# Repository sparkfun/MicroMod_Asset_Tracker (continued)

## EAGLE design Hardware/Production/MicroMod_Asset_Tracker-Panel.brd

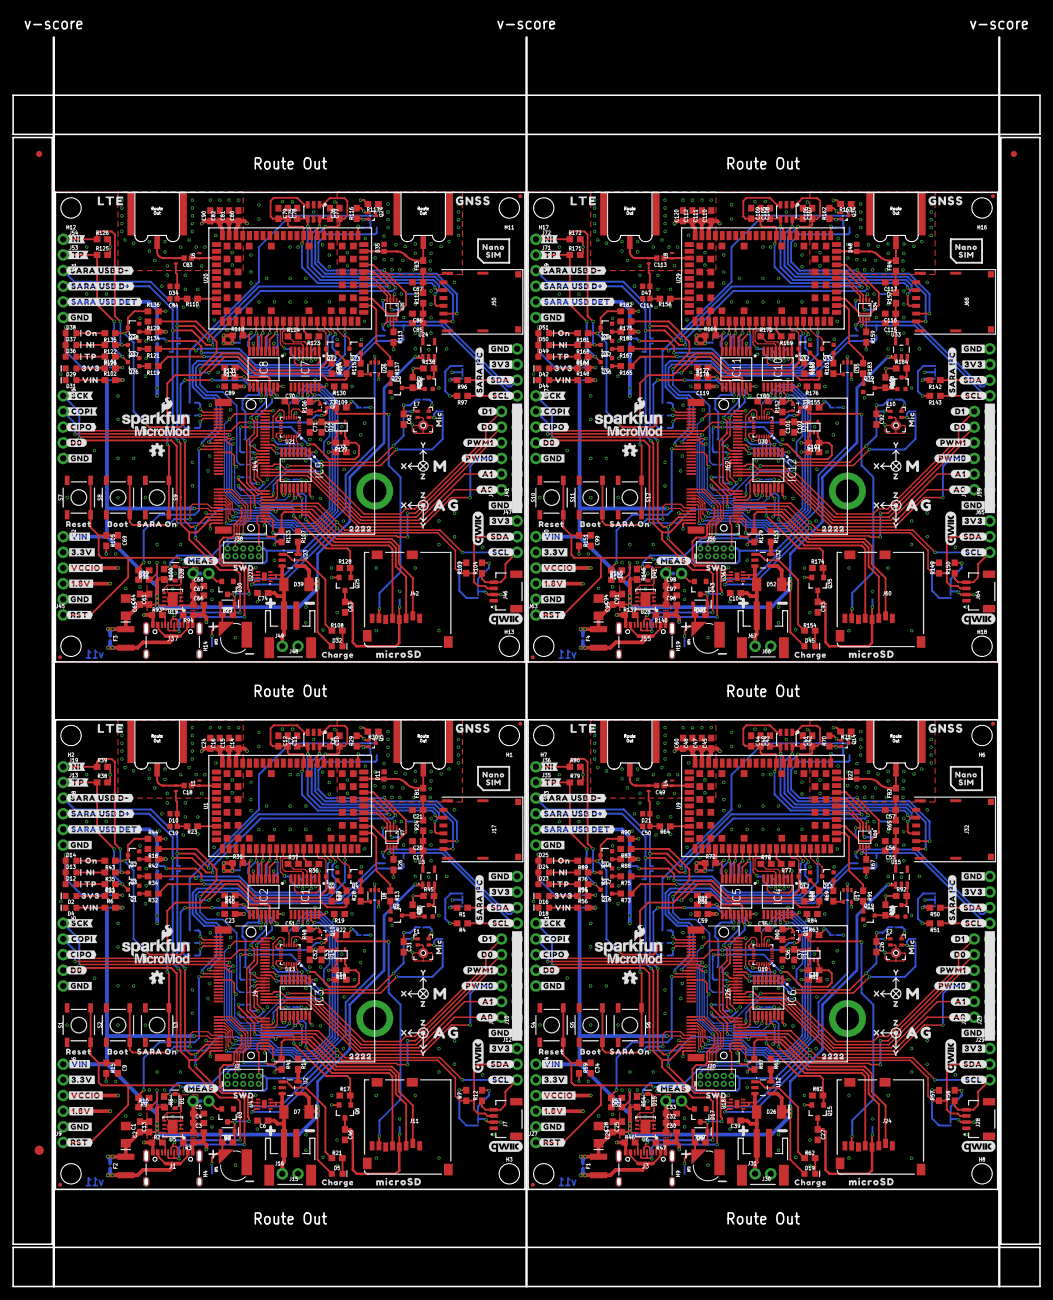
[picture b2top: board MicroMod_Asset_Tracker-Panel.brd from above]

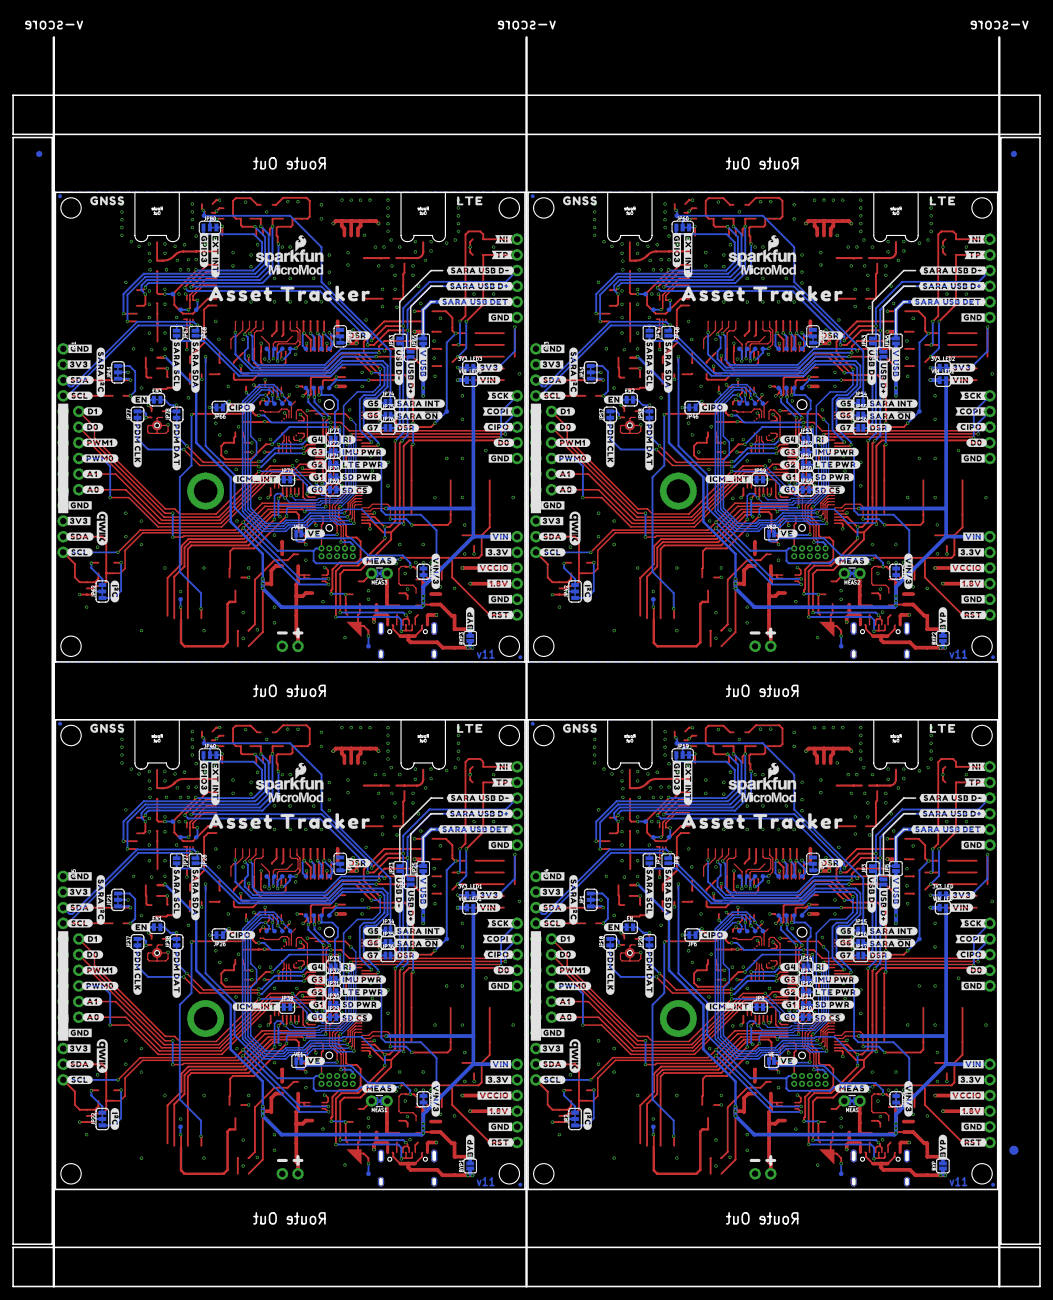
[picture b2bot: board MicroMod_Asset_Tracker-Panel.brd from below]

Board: 4 copper layers, 166.6 x 202.7 mm, 1354 parts (515 on the bottom side), 548 nets.

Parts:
3V3_LED, 3V3_LED1, 3V3_LED2, 3V3_LED3: SMT-JUMPER_2_NC_TRACE_SILK
BT1, BT2, BT3, BT4: ML414H; ML414H_IV01E
BYP, BYP1, BYP2, BYP3: JUMPER-SMT_2_NO_SILK; SMT-JUMPER_2_NO_SILK
C1, C4, C12, C14, C20, C22, C23, C26, C27, C28, C31, C32, C35, C36, C44, C45, C46, C51, C52, C56, C58, C59, C62, C63, C64, C67, C70, C71, C79, C80, C86, C88, C89, C92, C93, C94, C97, C100, C101, C109, C110, C116, C118, C119: 0.1uF; 0603
C2, C29, C65, C95: 10uF; EIA3216
C3, C6, C30, C39, C66, C74, C96, C104: 4.7uF; 0603
C5, C13, C25, C33, C61, C68, C91, C98: 0.22uF; 0603
C7, C8, C10, C11, C21, C40, C41, C42, C43, C57, C75, C76, C77, C78, C87, C105, C106, C107, C108, C117: 47pF; 0603
C9, C34, C69, C99: 1nF; 0603
C15, C47, C81, C111: 68pF; 0603
C16, C48, C82, C112: 10uF; 0603
C17, C37, C38, C53, C54, C55, C72, C73, C85, C102, C103, C115: 1.0uF; 0603
C18, C49, C83, C113: 33pF; 0402
C19, C50, C84, C114: 27pF; 0402
C24, C60, C90, C120: 15pF; 0603
D1, D15, D28, D41: 3.3V; SOD-323
D2, D16, D29, D42: RED; LED-0603
D3, D17, D30, D43: BAS70-05; SOT23-3
D4, D5, D18, D19, D31, D32, D44, D45: Yellow; LED-0603
D6, D9, D27, D40: 3A/10V/280mV; SOD-323
D7, D26, D39, D52: 1A/15V/220mV; DO-214BA
D8, D20, D33, D46: DT1042-04SO-7; SOT23-6L
D10, D11, D21, D22, D34, D35, D47, D48: PESD0402; 0402
D12, D23, D36, D49: GREEN; LED-0603
D13, D24, D37, D50: BLUE; LED-0603
D14, D25, D38, D51: WHITE; LED-0603
DSR, DSR1, DSR2, DSR3: JUMPER-SMT_3_1-NC_TRACE_SILK; SMT-JUMPER_3_1-NC_TRACE_SILK
E1, E2, E7, E10: SPH0641LM4H-1; SPH0641LM4H-1_MICROPHONE
E3, E5, E8, E11: LTE; SMA-EDGE-SMD
E4, E6, E9, E12: GNSS; SMA-EDGE-SMD
E$1, E$2, E$3, E$4: FIDUCIAL-1X2
E$5, E$6: FIDUCIAL-1.5X3
EN, EN1, EN2, EN3: SMT-JUMPER_2_NC_TRACE_SILK
F1, F2, F3, F4: 6V/2A; 1210
FB1, FB2, FB3, FB4: 30Ω/1.8A; 0603
FD1, FD2, FD3, FD4, FD5, FD6, FD7, FD8, FD9, FD10, FD11, FD12, FD13, FD14, FD15, FD16: FIDUCIALUFIDUCIAL; FIDUCIAL-MICRO
H1, H2, H3, H4, H6, H7, H8, H9, H11, H12, H13, H14, H16, H17, H18, H19: STAND-OFF
H5, H10, H15, H20: STAND-OFF-REFLOW2.5MM_TALL; STAND-OFF-REFLOW-M2.5
IC1, IC2, IC3, IC4, IC5, IC6, IC7, IC8, IC9, IC10, IC11, IC12: SN74AVC4T774PW; SOP65P640X120-16N
J1, J3, J37, J55: USB-C-16P_4LAYER-PADS
J2, J20, J38, J56: JTAG; 2X5-PTH-1.27MM
J4, J26, J44, J62: MICROMOD-2222-C; M.2-CONNECTOR-E
J5, J21, J39, J57: SPI; 1X05_NO_SILK
J6, J34, J52, J70: DIAG; 1X05_NO_SILK
J7, J28, J46, J64: QWIIC_RIGHT_ANGLE; JST04_1MM_RA
J8, J10, J22, J23, J40, J41, J58, J59: 1X06_NO_SILK
J9, J27, J45, J63: !RST!; 1X01_NO_SILK
J11, J24, J42, J60: microSD; MICRO-SD-SOCKET
J12, J14, J25, J29, J43, J47, J61, J65: 1X04_NO_SILK
J13, J35, J53, J71: TP; 1X01_NO_SILK
J15, J30, J48, J66: JST-2-SMD
J16, J31, J49, J67: 1X02_NO_SILK
J17, J32, J50, J68: NANO_SIM; NANO_SIM_WURTH_693043020611
J18, J33, J51, J69: SARA_USB; 1X04_NO_SILK
J19, J36, J54, J72: NI; 1X01_NO_SILK
JP1, JP2, JP21, JP22, JP41, JP42, JP61, JP62: SMT-JUMPER_3_2-NC_TRACE_SILK
JP3, JP4, JP5, JP7, JP8, JP13, JP14, JP15, JP16, JP17, JP23, JP24, JP25, JP27, JP28, JP32, JP33, JP34, JP35, JP36, JP43, JP44, JP45, JP47, JP48, JP52, JP53, JP54, JP55, JP56, JP63, JP64, JP65, JP67, JP68, JP72, JP73, JP74, JP75, JP76: JUMPER-SMT_2_NO_SILK; SMT-JUMPER_2_NO_SILK
JP6, JP9, JP10, JP11, JP12, JP18, JP20, JP26, JP29, JP30, JP31, JP37, JP38, JP39, JP46, JP49, JP50, JP51, JP57, JP58, JP59, JP66, JP69, JP70, JP71, JP77, JP78, JP79: JUMPER-SMT_2_NC_TRACE_SILK; SMT-JUMPER_2_NC_TRACE_SILK
JP19, JP40, JP60, JP80: JUMPER-SMT_3_1-NC_TRACE_SILK; SMT-JUMPER_3_1-NC_TRACE_SILK
L1, L4, L6, L8: DNP; 0402_COILCRAFT
L2, L3, L5, L7: 68nH; 0402_COILCRAFT
LOGO1, LOGO4, LOGO5, LOGO10, LOGO13, LOGO16, LOGO19, LOGO22: SFE_LOGO_NAME_FLAME.1_INCH; SFE_LOGO_NAME_FLAME_.1
LOGO2, LOGO6, LOGO7, LOGO8, LOGO11, LOGO12, LOGO14, LOGO17, LOGO18, LOGO20, LOGO23, LOGO24: QWIIC_LOGO_CONNECTOR; QWIIC_5.5MM
LOGO3, LOGO9, LOGO15, LOGO21: OSHW-LOGOMINI; OSHW-LOGO-MINI
MEAS, MEAS1, MEAS2, MEAS3: COMBO-JUMPER_2_NC_TRACE
Q1, Q2, Q3, Q4, Q7, Q8, Q9, Q12, Q13, Q16, Q17, Q18, Q19, Q20, Q22, Q23, Q26, Q27, Q28, Q29, Q30, Q32, Q33, Q36, Q37, Q38, Q39, Q40: 310mA/60V/1.6Ω; SOT323
Q5, Q10, Q11, Q14, Q21, Q24, Q31, Q34: 20V/0.2A/8MHz/1.2Ω/1Vth; SOT-416FL
Q6, Q15, Q25, Q35: 20V/4.2A/52mΩ/1.4W; SOT23-3
R1, R4, R7, R12, R14, R22, R29, R30, R48, R50, R51, R57, R58, R60, R61, R63, R70, R71, R96, R97, R103, R104, R106, R107, R109, R116, R117, R142, R143, R149, R150, R152, R153, R155, R162, R163: 2.2k; 0603
R2, R3, R46, R47, R93, R94, R139, R140: 5.1k; 0603
R5, R15, R16, R17, R18, R19, R20, R25, R38, R39, R40, R41, R44, R45, R54, R59, R66, R79, R80, R81, R82, R83, R84, R85, R86, R87, R90, R92, R100, R105, R112, R125, R126, R127, R128, R129, R130, R131, R132, R133, R136, R138, R146, R151, R158, R171, R172, R173, R174, R175, R176, R177, R178, R179, R182, R184: 100k; 0603
R6, R56, R102, R148: 4.7k; 0603
R8, R49, R95, R141: 3.3k; 0603
R9, R23, R52, R64, R98, R110, R144, R156: 10k; 0603
R10, R53, R99, R145: 20k; 0603
R11, R13, R21, R27, R28, R32, R34, R42, R43, R55, R62, R68, R69, R73, R75, R88, R89, R91, R101, R108, R114, R115, R119, R121, R134, R135, R137, R147, R154, R160, R161, R165, R167, R180, R181, R183: 1k; 0603
R24, R65, R111, R157: 10; 0603
R26, R67, R113, R159: 200k; 0603
R31, R36, R37, R72, R77, R78, R118, R123, R124, R164, R169, R170: 0; 0603
R33, R74, R120, R166: 100; 0603
R35, R76, R122, R168: 470; 0603
S1, S4, S7, S10: RESET; TACTILE_SWITCH_SMD_5.2MM
S2, S5, S8, S11: BOOT; TACTILE_SWITCH_SMD_5.2MM
S3, S6, S9, S12: SARA_PWR; TACTILE_SWITCH_SMD_5.2MM
TP1, TP2, TP3, TP4, TP5, TP6, TP7, TP8, TP9, TP10, TP11, TP12, TP13, TP14, TP15, TP16, TP17, TP18, TP19, TP20, TP21, TP22, TP23, TP24, TP25, TP26, TP27, TP28, TP29, TP30, TP31, TP32, TP33, TP34, TP35, TP36, TP37, TP38, TP39, TP40, TP41, TP42, TP43, TP44, TP45, TP46, TP47, TP48, TP49, TP50, TP51, TP52, TP53, TP54, TP55, TP56, TP57, TP58, TP59, TP60, TP61, TP62, TP63, TP64, TP65, TP66, TP67, TP68, TP69, TP70, TP71, TP72, TP73, TP74, TP75, TP76, TP77, TP78, TP79, TP80, TP81, TP82, TP83, TP84, TP85, TP86, TP87, TP88, TP89, TP90, TP91, TP92: TEST-POINT3; PAD.03X.03
U1, U9, U20, U29: SARA-R5; SARA-LGA
U2, U12, U23, U32: MCP73831; SOT23-5
U3, U15, U24, U33: 3.3V; SOT23-5
U4, U18, U27, U36: MAX17048; DFN-8
U5, U6, U19, U28: AP7361C-33FGE; UDFN-8
U7, U16, U25, U34: PCA9306; VSSOP_8PIN
U8, U17, U26, U35: 74HC1G04; SOT353
U10, U13, U21, U30: 9DoF IMU; QFN24-3X3-ICM-20948
U11, U14, U22, U31: 1.8V/100mA; SC70
U$1, U$223, U$354, U$485: #EN#0
U$2, U$222, U$353, U$484: MIC0
U$3, U$11, U$13, U$14, U$156, U$157, U$179, U$180, U$287, U$288, U$310, U$311, U$418, U$419, U$441, U$442: #3V3#1
U$4, U$176, U$307, U$438: #3V3#0
U$5, U$23, U$224, U$225, U$355, U$356, U$486, U$487: #SARA_I�C#0
U$6, U$7, U$144, U$145, U$275, U$276, U$406, U$407: #A0#5
U$8, U$9, U$146, U$147, U$277, U$278, U$408, U$409: #A1#4
U$10, U$25, U$35, U$68, U$148, U$149, U$254, U$255, U$279, U$280, U$385, U$386, U$410, U$411, U$516, U$517: #D0#1
U$12, U$15, U$16, U$22, U$158, U$159, U$181, U$182, U$289, U$290, U$312, U$313, U$420, U$421, U$443, U$444: #GND#0
U$17, U$86, U$174, U$211, U$305, U$342, U$436, U$473: #RST#1
U$18, U$175, U$306, U$437: #VE#0
U$19, U$87, U$171, U$212, U$302, U$343, U$433, U$474: #MEAS#2
U$20, U$177, U$308, U$439: #VIN#1
U$21, U$172, U$303, U$434: SWD0
U$24, U$34, U$120, U$121, U$263, U$264, U$394, U$395: MICROMOD_LOGO_.35
U$26, U$27, U$43, U$44, U$160, U$161, U$183, U$184, U$291, U$292, U$314, U$315, U$422, U$423, U$445, U$446: #SCL#3
U$28, U$178, U$309, U$440: MICROSD0
U$29, U$31, U$150, U$151, U$281, U$282, U$412, U$413: #D1#0
U$30, U$37, U$50, U$51, U$162, U$163, U$185, U$186, U$293, U$294, U$316, U$317, U$424, U$425, U$447, U$448: #SDA#2
U$32, U$41, U$152, U$153, U$283, U$284, U$414, U$415: #PWM0#3
U$33, U$173, U$304, U$435: #BYP#1
U$36, U$164, U$295, U$426: 3V37
U$38, U$48, U$169, U$188, U$300, U$319, U$431, U$450: Y2
U$39, U$47, U$168, U$189, U$299, U$320, U$430, U$451: X1
U$40, U$165, U$296, U$427: BOOT5
U$42, U$49, U$154, U$155, U$285, U$286, U$416, U$417: #PWM1#2
U$45, U$166, U$297, U$428: RESET6
U$46, U$167, U$298, U$429: VIN8
U$52, U$54, U$170, U$190, U$301, U$321, U$432, U$452: Z0
U$53, U$187, U$318, U$449: #I�C#0
U$55, U$56, U$73, U$74, U$81, U$82, U$138, U$139, U$142, U$143, U$191, U$192, U$269, U$270, U$273, U$274, U$322, U$323, U$400, U$401, U$404, U$405, U$453, U$454: #GND#4
U$57, U$58, U$193, U$194, U$324, U$325, U$455, U$456: #TP#0
U$59, U$60, U$195, U$196, U$326, U$327, U$457, U$458: #NI#0
U$61, U$62, U$63, U$64, U$197, U$198, U$199, U$200, U$328, U$329, U$330, U$331, U$459, U$460, U$461, U$462: #SARA_USB_D##0
U$65, U$66, U$201, U$202, U$332, U$333, U$463, U$464: #SARA_USB_DET#0
U$67, U$75, U$203, U$204, U$334, U$335, U$465, U$466: #VIN#0
U$69, U$70, U$132, U$135, U$265, U$266, U$396, U$397: #CIPO#2
U$71, U$72, U$136, U$137, U$267, U$268, U$398, U$399: #COPI#1
U$76, U$79, U$205, U$206, U$336, U$337, U$467, U$468: #3#3V#0
U$77, U$78, U$140, U$141, U$271, U$272, U$402, U$403: #SCK#0
U$80, U$83, U$207, U$208, U$338, U$339, U$469, U$470: #VCCIO#0
U$84, U$85, U$209, U$210, U$340, U$341, U$471, U$472: #1#8V#0
U$88, U$89, U$226, U$227, U$357, U$358, U$488, U$489: LTE0
U$90, U$213, U$344, U$475: NI0
U$91, U$214, U$345, U$476: TP0
U$92, U$93, U$215, U$216, U$346, U$347, U$477, U$478: #USB_D##0
U$94, U$217, U$348, U$479: #V_USB#0
U$95, U$218, U$349, U$480: AG0
U$96, U$219, U$350, U$481: M0
U$97, U$220, U$351, U$482: CHARGE0
U$98, U$221, U$352, U$483: ASSET_TRACKER0
U$99, U$100, U$228, U$229, U$359, U$360, U$490, U$491: GNSS0
U$101, U$242, U$373, U$504: ON0
U$102, U$105, U$232, U$245, U$363, U$376, U$494, U$507: #DSR#0
U$103, U$230, U$361, U$492: #SARA_INT#0
U$104, U$231, U$362, U$493: #RI#0
U$106, U$233, U$364, U$495: #SD_#CS##0
U$107, U$234, U$365, U$496: #IMU_PWR#0
U$108, U$235, U$366, U$497: #LTE_PWR#0
U$109, U$236, U$367, U$498: #SD_PWR#0
U$110, U$260, U$391, U$522: #SARA_#ON##0
U$111, U$237, U$368, U$499: #SARA_SCL#0
U$112, U$238, U$369, U$500: #SARA_SDA#0
U$113, U$241, U$372, U$503: SARA_ON0
U$114, U$239, U$370, U$501: #CIPO#0
U$115, U$240, U$371, U$502: 22220
U$116, U$243, U$374, U$505: #PDM_CLK#0
U$117, U$244, U$375, U$506: #PDM_DAT#0
U$118, U$261, U$392, U$523: #EXT_INT#0
U$119, U$262, U$393, U$524: #GPIO3#0
U$122, U$246, U$377, U$508: #G0#0
U$123, U$247, U$378, U$509: #G1#0
U$124, U$248, U$379, U$510: #G2#0
U$125, U$249, U$380, U$511: #G3#0
U$126, U$250, U$381, U$512: #G4#0
U$127, U$251, U$382, U$513: #G7#0
U$128, U$252, U$383, U$514: #G6#0
U$129, U$253, U$384, U$515: #G5#0
U$130, U$256, U$387, U$518: NANO0
U$131, U$257, U$388, U$519: SIM0
U$133, U$258, U$389, U$520: #VIN#3#0
U$134, U$259, U$390, U$521: #ICM_INT#0
VE, VE1, VE2, VE3: SMT-JUMPER_2_NO_SILK
VIN/1, VIN/2, VIN/3, VIN/4: JUMPER-SMT_2_NC_TRACE_SILK; SMT-JUMPER_2_NC_TRACE_SILK
VIN_LED, VIN_LED1, VIN_LED2, VIN_LED3: SMT-JUMPER_2_NC_TRACE_SILK

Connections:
1.8V: C52.1, C53.1, IC3.1, IC3.16, J6.4, Q10.1, R48.2, U13.8, U13.13, U14.5
1.8V1: C36.1, C37.1, IC6.1, IC6.16, J34.4, Q11.1, R60.2, U10.8, U10.13, U11.5
1.8V2: C71.1, C72.1, IC9.1, IC9.16, J52.4, Q21.1, R106.2, U21.8, U21.13, U22.5
1.8V3: C101.1, C102.1, IC12.1, IC12.16, J70.4, Q31.1, R152.2, U30.8, U30.13, U31.5
3.3V: 3V3_LED.2, C14.1, C15.1, C16.1, C24.1, C31.1, C54.1, D3.2, D12.A, D13.A, D14.A, EN.2, IC1.15, IC2.15, IC3.15, J2.1, J4.2, J4.74, J6.2, J7.2, J12.2, J14.2, JP1.2, JP2.2, JP6.2, MEAS.2, MEAS.4, Q6.2, R15.2, R16.2, R25.1, R26.2, R30.2, R38.2, R39.2, R41.2, R44.2, R45.1, U1.51, U1.52, U1.53, U8.5, U14.1
3.3V1: 3V3_LED1.2, C26.1, C38.1, C45.1, C47.1, C48.1, C60.1, D17.2, D23.A, D24.A, D25.A, EN1.2, IC4.15, IC5.15, IC6.15, J20.1, J25.2, J26.2, J26.74, J28.2, J29.2, J34.2, JP21.2, JP22.2, JP26.2, MEAS1.2, MEAS1.4, Q15.2, R59.2, R66.1, R67.2, R71.2, R79.2, R80.2, R81.2, R87.2, R90.2, R92.1, U9.51, U9.52, U9.53, U11.1, U17.5
3.3V2: 3V3_LED2.2, C62.1, C73.1, C80.1, C81.1, C82.1, C90.1, D30.2, D36.A, D37.A, D38.A, EN2.2, IC7.15, IC8.15, IC9.15, J38.1, J43.2, J44.2, J44.74, J46.2, J47.2, J52.2, JP41.2, JP42.2, JP46.2, MEAS2.2, MEAS2.4, Q25.2, R105.2, R112.1, R113.2, R117.2, R125.2, R126.2, R127.2, R133.2, R136.2, R138.1, U20.51, U20.52, U20.53, U22.1, U26.5
3.3V3: 3V3_LED3.2, C92.1, C103.1, C110.1, C111.1, C112.1, C120.1, D43.2, D49.A, D50.A, D51.A, EN3.2, IC10.15, IC11.15, IC12.15, J56.1, J61.2, J62.2, J62.74, J64.2, J65.2, J70.2, JP61.2, JP62.2, JP66.2, MEAS3.2, MEAS3.4, Q35.2, R151.2, R158.1, R159.2, R163.2, R171.2, R172.2, R173.2, R179.2, R182.2, R184.1, U29.51, U29.52, U29.53, U31.1, U35.5
3.3V_EN: J4.4, VE.1
3.3V_EN1: J26.4, VE1.1
3.3V_EN2: J44.4, VE2.1
3.3V_EN3: J62.4, VE3.1
!BOOT!: J4.11, S2.3, S2.4
!BOOT!1: J26.11, S5.3, S5.4
!BOOT!2: J44.11, S8.3, S8.4
!BOOT!3: J62.11, S11.3, S11.4
!RESET!: C9.1, J2.10, J4.6, J9.1, R15.1, S1.3, S1.4, U8.2
!RESET!1: C34.1, J20.10, J26.6, J27.1, R59.1, S4.3, S4.4, U17.2
!RESET!2: C69.1, J38.10, J44.6, J45.1, R105.1, S7.3, S7.4, U26.2
!RESET!3: C99.1, J56.10, J62.6, J63.1, R151.1, S10.3, S10.4, U35.2
A0: J4.34, J8.1
A1: J4.38, J8.2
A2: J22.1, J26.34
A3: J22.2, J26.38
A4: J40.1, J44.34
A5: J40.2, J44.38
A6: J58.1, J62.34
A7: J58.2, J62.38
ANT_GNSS_PWR_EN: R13.1, U1.23
ANT_GNSS_PWR_EN1: R91.1, U9.23
ANT_GNSS_PWR_EN2: R137.1, U20.23
ANT_GNSS_PWR_EN3: R183.1, U29.23
ANT_REG_EN: Q9.3, R45.2, U3.3
ANT_REG_EN1: Q20.3, R92.2, U15.3
ANT_REG_EN2: Q30.3, R138.2, U24.3
ANT_REG_EN3: Q40.3, R184.2, U33.3
CHG_LED: R21.1, U2.1
CHG_LED1: R62.1, U12.1
CHG_LED2: R108.1, U23.1
CHG_LED3: R154.1, U32.1
CTS1: IC1.12, J4.15, TP7.P$1
CTS2: IC4.12, J26.15, TP30.P$1
CTS3: IC7.12, J44.15, TP53.P$1
CTS4: IC10.12, J62.15, TP76.P$1
D0: J4.10, J5.4, J8.5
D1: J4.18, J8.6
D2: J22.6, J26.18
D3: J21.4, J22.5, J26.10
D4: J40.6, J44.18
D5: J39.4, J40.5, J44.10
D6: J58.6, J62.18
D7: J57.4, J58.5, J62.10
DCD: IC2.13, J4.20, TP19.P$1
DCD1: IC5.13, J26.20, TP40.P$1
DCD2: IC8.13, J44.20, TP63.P$1
DCD3: IC11.13, J62.20, TP86.P$1
DSR: IC2.11, JP17.2, R20.2, TP21.P$1
DSR1: IC5.11, JP36.2, R85.2, TP42.P$1
DSR2: IC8.11, JP56.2, R131.2, TP65.P$1
DSR3: IC11.11, JP76.2, R177.2, TP88.P$1
DTR: IC2.14, J4.22, R40.1, TP18.P$1
DTR1: IC5.14, J26.22, R86.1, TP39.P$1
DTR2: IC8.14, J44.22, R132.1, TP62.P$1
DTR3: IC11.14, J62.22, R178.1, TP85.P$1
G0: J4.40, JP10.1
G1: J4.42, JP11.1
G2: J4.44, JP12.1
G3: J4.46, JP13.1
G4: J4.48, JP14.1
G5: J4.73, JP15.1
G6: J4.71, JP16.1
G7: J4.69, JP17.1
G8: J26.40, JP29.1
G9: J26.42, JP30.1
G10: J26.44, JP31.1
G11: J26.46, JP32.1
G12: J26.48, JP33.1
G13: J26.73, JP34.1
G14: J26.71, JP35.1
G15: J26.69, JP36.1
G16: J44.40, JP49.1
G17: J44.42, JP50.1
G18: J44.44, JP51.1
G19: J44.46, JP52.1
G20: J44.48, JP53.1
G21: J44.73, JP54.1
G22: J44.71, JP55.1
G23: J44.69, JP56.1
G24: J62.40, JP69.1
G25: J62.42, JP70.1
G26: J62.44, JP71.1
G27: J62.46, JP72.1
G28: J62.48, JP73.1
G29: J62.73, JP74.1
G30: J62.71, JP75.1
G31: J62.69, JP76.1
GND: BT1.-, C1.2, C2.-, C3.2, C4.2, C5.2, C6.2, C7.2, C8.2, C9.2, C10.1, C11.1, C12.1, C13.2, C14.2, C15.2, C16.2, C17.2, C19.2, C20.2, C21.2, C22.2, C23.2, C24.2, C31.2, C46.2, C51.2, C52.2, C53.2, C54.2, D1.A, D2.C, D4.C, D8.2, D8.5, D10.2, D11.2, DSR.1, E1.2, E1.3, E1.6, E1.7, E1.8, E3.GND@0, E3.GND@1, E4.GND@0, E4.GND@1, H5.1, IC1.2, IC1.8, IC1.9, IC1.10, IC2.1, IC2.9, IC2.10, IC3.2, IC3.7, IC3.8, IC3.9, IC3.10, J1.GND, J1.GND2, J2.3, J2.5, J2.9, J4.1, J4.7, J4.33, J4.36, J4.39, J4.45, J4.75, J5.5, J6.5, J7.1, J10.1, J10.2, J10.3, J10.4, J10.5, J10.6, J11.CD1, J11.GND, J11.GND1, J11.GND3, J12.1, J14.1, J15.1, J16.2, J17.C5, J18.4, L1.P$2, Q1.2, Q2.2, Q3.2, Q4.2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
GND1: BT2.-, C25.2, C26.2, C27.2, C28.2, C29.-, C30.2, C32.2, C33.2, C34.2, C35.2, C36.2, C37.2, C38.2, C39.2, C40.2, C41.2, C42.1, C43.1, C44.1, C45.2, C47.2, C48.2, C50.2, C55.2, C56.2, C57.2, C58.2, C59.2, C60.2, D15.A, D16.C, D18.C, D20.2, D20.5, D21.2, D22.2, DSR1.1, E2.2, E2.3, E2.6, E2.7, E2.8, E5.GND@0, E5.GND@1, E6.GND@0, E6.GND@1, H10.1, IC4.2, IC4.8, IC4.9, IC4.10, IC5.1, IC5.9, IC5.10, IC6.2, IC6.7, IC6.8, IC6.9, IC6.10, J3.GND, J3.GND2, J20.3, J20.5, J20.9, J21.5, J23.1, J23.2, J23.3, J23.4, J23.5, J23.6, J24.CD1, J24.GND, J24.GND1, J24.GND3, J25.1, J26.1, J26.7, J26.33, J26.36, J26.39, J26.45, J26.75, J28.1, J29.1, J30.1, J31.2, J32.C5, J33.4, J34.5, L4.P$2, Q12.2, Q13.2, Q16.2, Q17.2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
GND2: BT3.-, C61.2, C62.2, C63.2, C64.2, C65.-, C66.2, C67.2, C68.2, C69.2, C70.2, C71.2, C72.2, C73.2, C74.2, C75.2, C76.2, C77.1, C78.1, C79.1, C80.2, C81.2, C82.2, C84.2, C85.2, C86.2, C87.2, C88.2, C89.2, C90.2, D28.A, D29.C, D31.C, D33.2, D33.5, D34.2, D35.2, DSR2.1, E7.2, E7.3, E7.6, E7.7, E7.8, E8.GND@0, E8.GND@1, E9.GND@0, E9.GND@1, H15.1, IC7.2, IC7.8, IC7.9, IC7.10, IC8.1, IC8.9, IC8.10, IC9.2, IC9.7, IC9.8, IC9.9, IC9.10, J37.GND, J37.GND2, J38.3, J38.5, J38.9, J39.5, J41.1, J41.2, J41.3, J41.4, J41.5, J41.6, J42.CD1, J42.GND, J42.GND1, J42.GND3, J43.1, J44.1, J44.7, J44.33, J44.36, J44.39, J44.45, J44.75, J46.1, J47.1, J48.1, J49.2, J50.C5, J51.4, J52.5, L6.P$2, Q22.2, Q23.2, Q26.2, Q27.2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
GND3: BT4.-, C91.2, C92.2, C93.2, C94.2, C95.-, C96.2, C97.2, C98.2, C99.2, C100.2, C101.2, C102.2, C103.2, C104.2, C105.2, C106.2, C107.1, C108.1, C109.1, C110.2, C111.2, C112.2, C114.2, C115.2, C116.2, C117.2, C118.2, C119.2, C120.2, D41.A, D42.C, D44.C, D46.2, D46.5, D47.2, D48.2, DSR3.1, E10.2, E10.3, E10.6, E10.7, E10.8, E11.GND@0, E11.GND@1, E12.GND@0, E12.GND@1, H20.1, IC10.2, IC10.8, IC10.9, IC10.10, IC11.1, IC11.9, IC11.10, IC12.2, IC12.7, IC12.8, IC12.9, IC12.10, J55.GND, J55.GND2, J56.3, J56.5, J56.9, J57.5, J59.1, J59.2, J59.3, J59.4, J59.5, J59.6, J60.CD1, J60.GND, J60.GND1, J60.GND3, J61.1, J62.1, J62.7, J62.33, J62.36, J62.39, J62.45, J62.75, J64.1, J65.1, J66.1, J67.2, J68.C5, J69.4, J70.5, L8.P$2, Q32.2, Q33.2, Q36.2, Q37.2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
I2C_SCL: J4.14, J7.4, J12.4, R12.1, U4.7
I2C_SCL1: J26.14, J28.4, J29.4, R58.1, U18.7
I2C_SCL2: J44.14, J46.4, J47.4, R104.1, U27.7
I2C_SCL3: J62.14, J64.4, J65.4, R150.1, U36.7
I2C_SDA: J4.12, J7.3, J12.3, R7.1, U4.8
I2C_SDA1: J26.12, J28.3, J29.3, R57.1, U18.8
I2C_SDA2: J44.12, J46.3, J47.3, R103.1, U27.8
I2C_SDA3: J62.12, J64.3, J65.3, R149.1, U36.8
I2S_SCK/PDM_CLK: E1.4, JP18.2
I2S_SCK/PDM_CLK1: E2.4, JP37.2
I2S_SCK/PDM_CLK2: E7.4, JP57.2
I2S_SCK/PDM_CLK3: E10.4, JP77.2
I2S_WS/PDM_DAT: E1.1, JP20.2
I2S_WS/PDM_DAT1: E2.1, JP38.2
I2S_WS/PDM_DAT2: E7.1, JP58.2
I2S_WS/PDM_DAT3: E10.1, JP78.2
ICM-20948-LV_!CS!: IC3.6, U13.22
ICM-20948-LV_!CS!1: IC6.6, U10.22
ICM-20948-LV_!CS!2: IC9.6, U21.22
ICM-20948-LV_!CS!3: IC12.6, U30.22
ICM-20948-LV_INT: IC3.3, U13.12
ICM-20948-LV_INT1: IC6.3, U10.12
ICM-20948-LV_INT2: IC9.3, U21.12
ICM-20948-LV_INT3: IC12.3, U30.12
ICM-20948-LV_SCK: IC3.5, U13.23
ICM-20948-LV_SCK1: IC6.5, U10.23
ICM-20948-LV_SCK2: IC9.5, U21.23
ICM-20948-LV_SCK3: IC12.5, U30.23
ICM-20948-LV_SDI: IC3.4, U13.24
ICM-20948-LV_SDI1: IC6.4, U10.24
ICM-20948-LV_SDI2: IC9.4, U21.24
ICM-20948-LV_SDI3: IC12.4, U30.24
ICM-20948-LV_SDO: Q10.2, R48.1, U13.9
ICM-20948-LV_SDO1: Q11.2, R60.1, U10.9
ICM-20948-LV_SDO2: Q21.2, R106.1, U21.9
ICM-20948-LV_SDO3: Q31.2, R152.1, U30.9
ICM_!CS!: IC3.11, J4.55
ICM_!CS!1: IC6.11, J26.55
ICM_!CS!2: IC9.11, J44.55
ICM_!CS!3: IC12.11, J62.55
ICM_INT: IC3.14, JP9.1
ICM_INT1: IC6.14, JP39.1
ICM_INT2: IC9.14, JP59.1
ICM_INT3: IC12.14, JP79.1
ICM_PWR: JP13.2, R16.1, U14.3
ICM_PWR1: JP32.2, R81.1, U11.3
ICM_PWR2: JP52.2, R127.1, U22.3
ICM_PWR3: JP72.2, R173.1, U31.3
LTE_PWR_ON: JP12.2, R18.1, R27.1
LTE_PWR_ON1: JP31.2, R68.1, R83.1
LTE_PWR_ON2: JP51.2, R114.1, R129.1
LTE_PWR_ON3: JP71.2, R160.1, R175.1
MICROSD_PWR: JP11.2, Q6.1, R17.2
MICROSD_PWR1: JP30.2, Q15.1, R82.2
MICROSD_PWR2: JP50.2, Q25.1, R128.2
MICROSD_PWR3: JP70.2, Q35.1, R174.2
unnamed: R6.2, VIN_LED.1
unnamed: JP1.3, R4.2
unnamed: JP1.1, R1.2
unnamed: E1.5, EN.1
unnamed: J4.53, JP7.2
unnamed: 3V3_LED.1, R11.2
unnamed: D2.A, R11.1
unnamed: D4.A, R6.1
unnamed: JP2.3, R12.2
unnamed: J1.A5, R2.2
unnamed: J1.B5, R3.2
unnamed: D1.C, R5.1, U5.5, VE.2
unnamed: JP2.1, R7.2
unnamed: BT1.+, D6.A, R8.1, TP24.P$1
unnamed: C18.2, E3.SIG, L2.P$2
unnamed: C19.1, D10.1, L2.P$1, R23.2
unnamed: J4.51, JP8.2
unnamed: R10.2, VIN/3.1
unnamed: J4.16, JP9.2
unnamed: R14.2, U2.5
unnamed: D5.C, R21.2
unnamed: R26.1, U7.P7, U7.P8
unnamed: DSR.2, IC2.8
unnamed: C17.1, C20.1, R24.1, U3.5
unnamed: C21.1, FB1.1, R24.2, TP22.P$1
unnamed: Q2.1, R27.2
unnamed: Q4.1, R28.2
unnamed: R28.1, U8.4
unnamed: JP6.1, R22.2
unnamed: C51.1, U13.10
unnamed: R31.2, U1.4
unnamed: Q1.1, R32.2
unnamed: J13.1, Q1.3, R33.1, R38.1
unnamed: D12.C, R33.2
unnamed: Q3.1, R34.2
unnamed: J19.1, Q3.3, R35.1, R39.1
unnamed: D13.C, R35.2
unnamed: R36.2, U1.13
unnamed: R37.2, U1.12
unnamed: Q8.1, R13.2
unnamed: J3.A5, R46.2
unnamed: Q8.3, Q9.1, R25.2
unnamed: JP19.2, Q5.2, R29.1
unnamed: J3.B5, R47.2
unnamed: BT2.+, D9.A, R49.1, TP46.P$1
unnamed: JP21.3, R51.2
unnamed: Q7.1, R42.2
unnamed: JP21.1, R50.2
unnamed: D14.C, R43.2
unnamed: E2.5, EN1.1
unnamed: J4.52, JP20.1
unnamed: J4.50, JP18.1
unnamed: 3V3_LED1.1, R55.2
unnamed: D16.A, R55.1
unnamed: R56.2, VIN_LED1.1
unnamed: D18.A, R56.1
unnamed: D15.C, R54.1, U6.5, VE1.2
unnamed: JP22.3, R58.2
unnamed: JP22.1, R57.2
unnamed: C35.1, U10.10
unnamed: R61.2, U12.5
unnamed: D19.C, R62.2
unnamed: C49.2, E5.SIG, L3.P$2
unnamed: C50.1, D21.1, L3.P$1, R64.2
unnamed: C55.1, C56.1, R65.1, U15.5
unnamed: C57.1, FB2.1, R65.2, TP44.P$1
unnamed: R67.1, U16.P7, U16.P8
unnamed: Q12.1, R68.2
unnamed: Q13.1, R69.2
unnamed: R69.1, U17.4
unnamed: JP26.1, R63.2
unnamed: R72.2, U9.4
unnamed: Q16.1, R73.2
unnamed: J35.1, Q16.3, R74.1, R79.1
unnamed: D23.C, R74.2
unnamed: Q17.1, R75.2
unnamed: J36.1, Q17.3, R76.1, R80.1
unnamed: D24.C, R76.2
unnamed: R77.2, U9.13
unnamed: R78.2, U9.12
unnamed: J26.53, JP27.2
unnamed: J26.51, JP28.2
unnamed: Q18.1, R88.2
unnamed: J26.52, JP38.1
unnamed: J26.50, JP37.1
unnamed: D25.C, R89.2
unnamed: DSR1.2, IC5.8
unnamed: R53.2, VIN/1.1
unnamed: J26.16, JP39.2
unnamed: Q19.1, R91.2
unnamed: Q19.3, Q20.1, R66.2
unnamed: JP40.2, Q14.2, R70.1
unnamed: J37.A5, R93.2
unnamed: J37.B5, R94.2
unnamed: BT3.+, D27.A, R95.1, TP69.P$1
unnamed: JP41.3, R97.2
unnamed: JP41.1, R96.2
unnamed: E7.5, EN2.1
unnamed: 3V3_LED2.1, R101.2
unnamed: D29.A, R101.1
unnamed: R102.2, VIN_LED2.1
unnamed: D31.A, R102.1
unnamed: D28.C, R100.1, U19.5, VE2.2
unnamed: JP42.3, R104.2
unnamed: JP42.1, R103.2
unnamed: C70.1, U21.10
unnamed: R107.2, U23.5
unnamed: D32.C, R108.2
unnamed: C83.2, E8.SIG, L5.P$2
unnamed: C84.1, D34.1, L5.P$1, R110.2
unnamed: C85.1, C86.1, R111.1, U24.5
unnamed: C87.1, FB3.1, R111.2, TP67.P$1
unnamed: R113.1, U25.P7, U25.P8
unnamed: Q22.1, R114.2
unnamed: Q23.1, R115.2
unnamed: R115.1, U26.4
unnamed: JP46.1, R109.2
unnamed: R118.2, U20.4
unnamed: Q26.1, R119.2
unnamed: J53.1, Q26.3, R120.1, R125.1
unnamed: D36.C, R120.2
unnamed: Q27.1, R121.2
unnamed: J54.1, Q27.3, R122.1, R126.1
unnamed: D37.C, R122.2
unnamed: R123.2, U20.13
unnamed: R124.2, U20.12
unnamed: J44.53, JP47.2
unnamed: J44.51, JP48.2
unnamed: Q28.1, R134.2
unnamed: J44.52, JP58.1
unnamed: J44.50, JP57.1
unnamed: D38.C, R135.2
unnamed: DSR2.2, IC8.8
unnamed: R99.2, VIN/2.1
unnamed: J44.16, JP59.2
unnamed: Q29.1, R137.2
unnamed: Q29.3, Q30.1, R112.2
unnamed: JP60.2, Q24.2, R116.1
unnamed: J55.A5, R139.2
unnamed: J55.B5, R140.2
unnamed: BT4.+, D40.A, R141.1, TP92.P$1
unnamed: JP61.3, R143.2
unnamed: JP61.1, R142.2
unnamed: E10.5, EN3.1
unnamed: 3V3_LED3.1, R147.2
unnamed: D42.A, R147.1
unnamed: R148.2, VIN_LED3.1
unnamed: D44.A, R148.1
unnamed: D41.C, R146.1, U28.5, VE3.2
unnamed: JP62.3, R150.2
unnamed: JP62.1, R149.2
unnamed: C100.1, U30.10
unnamed: R153.2, U32.5
unnamed: D45.C, R154.2
unnamed: C113.2, E11.SIG, L7.P$2
unnamed: C114.1, D47.1, L7.P$1, R156.2
unnamed: C115.1, C116.1, R157.1, U33.5
unnamed: C117.1, FB4.1, R157.2, TP90.P$1
unnamed: R159.1, U34.P7, U34.P8
unnamed: Q32.1, R160.2
unnamed: Q33.1, R161.2
unnamed: R161.1, U35.4
unnamed: JP66.1, R155.2
unnamed: R164.2, U29.4
unnamed: Q36.1, R165.2
unnamed: J71.1, Q36.3, R166.1, R171.1
unnamed: D49.C, R166.2
unnamed: Q37.1, R167.2
unnamed: J72.1, Q37.3, R168.1, R172.1
unnamed: D50.C, R168.2
unnamed: R169.2, U29.13
unnamed: R170.2, U29.12
unnamed: J62.53, JP67.2
unnamed: J62.51, JP68.2
unnamed: Q38.1, R180.2
unnamed: J62.52, JP78.1
unnamed: J62.50, JP77.1
unnamed: D51.C, R181.2
unnamed: DSR3.2, IC11.8
unnamed: R145.2, VIN/4.1
unnamed: J62.16, JP79.2
unnamed: Q39.1, R183.2
unnamed: Q39.3, Q40.1, R158.2
unnamed: JP80.2, Q34.2, R162.1
PWM0: J4.32, J8.3
PWM1: J4.47, J8.4
PWM2: J22.3, J26.32
PWM3: J22.4, J26.47
PWM4: J40.3, J44.32
PWM5: J40.4, J44.47
PWM6: J58.3, J62.32
PWM7: J58.4, J62.47
RI: IC2.12, JP14.2, TP20.P$1
RI1: IC5.12, JP33.2, TP41.P$1
RI2: IC8.12, JP53.2, TP64.P$1
RI3: IC11.12, JP73.2, TP87.P$1
RTC_3V: D3.3, D6.C, J4.72, R8.2
RTC_3V1: D9.C, D17.3, J26.72, R49.2
RTC_3V2: D27.C, D30.3, J44.72, R95.2
RTC_3V3: D40.C, D43.3, J62.72, R141.2
RTS1: IC1.11, J4.13, R19.2, TP8.P$1
RTS2: IC4.11, J26.13, R84.2, TP31.P$1
RTS3: IC7.11, J44.13, R130.2, TP54.P$1
RTS4: IC10.11, J62.13, R176.2, TP77.P$1
RX1: IC1.14, J4.19, TP5.P$1
RX2: IC4.14, J26.19, TP28.P$1
RX3: IC7.14, J44.19, TP51.P$1
RX4: IC10.14, J62.19, TP74.P$1
SARA_!ON!: JP16.2, Q7.3, R43.1, R44.1, TP13.P$1
SARA_!ON!1: JP35.2, Q18.3, R89.1, R90.1, TP43.P$1
SARA_!ON!2: JP55.2, Q28.3, R135.1, R136.1, TP66.P$1
SARA_!ON!3: JP75.2, Q38.3, R181.1, R182.1, TP89.P$1
SARA_!RESET!: Q4.3, U1.18
SARA_!RESET!1: Q13.3, U9.18
SARA_!RESET!2: Q23.3, U20.18
SARA_!RESET!3: Q33.3, U29.18
SARA_ANT: C18.1, L1.P$1, U1.56
SARA_ANT1: C49.1, L4.P$1, U9.56
SARA_ANT2: C83.1, L6.P$1, U20.56
SARA_ANT3: C113.1, L8.P$1, U29.56
SARA_ANT_DET: R23.1, U1.62
SARA_ANT_DET1: R64.1, U9.62
SARA_ANT_DET2: R110.1, U20.62
SARA_ANT_DET3: R156.1, U29.62
SARA_ANT_GNSS: D11.1, E4.SIG, FB1.2, U1.31
SARA_ANT_GNSS1: D22.1, E6.SIG, FB2.2, U9.31
SARA_ANT_GNSS2: D35.1, E9.SIG, FB3.2, U20.31
SARA_ANT_GNSS3: D48.1, E12.SIG, FB4.2, U29.31
SARA_CTS: IC1.5, TP3.P$1, U1.11
SARA_CTS1: IC4.5, TP26.P$1, U9.11
SARA_CTS2: IC7.5, TP49.P$1, U20.11
SARA_CTS3: IC10.5, TP72.P$1, U29.11
SARA_DCD/RXD2O: IC2.4, TP15.P$1, U1.8
SARA_DCD/RXD2O1: IC5.4, TP36.P$1, U9.8
SARA_DCD/RXD2O2: IC8.4, TP59.P$1, U20.8
SARA_DCD/RXD2O3: IC11.4, TP82.P$1, U29.8
SARA_DSR/RTS2I: IC2.6, TP17.P$1, U1.6
SARA_DSR/RTS2I1: IC5.6, TP38.P$1, U9.6
SARA_DSR/RTS2I2: IC8.6, TP61.P$1, U20.6
SARA_DSR/RTS2I3: IC11.6, TP84.P$1, U29.6
SARA_DTR/TXD2I: IC2.3, TP14.P$1, U1.9
SARA_DTR/TXD2I1: IC5.3, TP35.P$1, U9.9
SARA_DTR/TXD2I2: IC8.3, TP58.P$1, U20.9
SARA_DTR/TXD2I3: IC11.3, TP81.P$1, U29.9
SARA_EXT_INT: JP19.3, U1.33
SARA_EXT_INT1: JP40.3, U9.33
SARA_EXT_INT2: JP60.3, U20.33
SARA_EXT_INT3: JP80.3, U29.33
SARA_GPIO1: JP40.1, U9.24
SARA_GPIO2: JP60.1, U20.24
SARA_GPIO3: JP19.1, U1.24
SARA_GPIO4: JP80.1, U29.24
SARA_INT: JP15.2, Q5.3, R30.1, TP12.P$1
SARA_INT1: JP34.2, Q14.3, R71.1, TP34.P$1
SARA_INT2: JP54.2, Q24.3, R117.1, TP57.P$1
SARA_INT3: JP74.2, Q34.3, R163.1, TP80.P$1
SARA_NI: R34.1, U1.16
SARA_NI1: R75.1, U9.16
SARA_NI2: R121.1, U20.16
SARA_NI3: R167.1, U29.16
SARA_PWR_ON: Q2.3, S3.1, S3.2, U1.15
SARA_PWR_ON1: Q12.3, S6.1, S6.2, U9.15
SARA_PWR_ON2: Q22.3, S9.1, S9.2, U20.15
SARA_PWR_ON3: Q32.3, S12.1, S12.2, U29.15
SARA_RI/CTS2O: IC2.5, TP16.P$1, U1.7
SARA_RI/CTS2O1: IC5.5, TP37.P$1, U9.7
SARA_RI/CTS2O2: IC8.5, TP60.P$1, U20.7
SARA_RI/CTS2O3: IC11.5, TP83.P$1, U29.7
SARA_RTS: IC1.6, TP4.P$1, U1.10
SARA_RTS1: IC4.6, TP27.P$1, U9.10
SARA_RTS2: IC7.6, TP50.P$1, U20.10
SARA_RTS3: IC10.6, TP73.P$1, U29.10
SARA_RXD: IC1.3, R36.1, TP1.P$1
SARA_RXD1: IC4.3, R77.1, TP11.P$1
SARA_RXD2: IC7.3, R123.1, TP47.P$1
SARA_RXD3: IC10.3, R169.1, TP70.P$1
SARA_SCL: J14.4, JP7.1, R4.1, U7.P6
SARA_SCL1: J25.4, JP27.1, R51.1, U16.P6
SARA_SCL2: J43.4, JP47.1, R97.1, U25.P6
SARA_SCL3: J61.4, JP67.1, R143.1, U34.P6
SARA_SCL_1.8V: TP10.P$1, U1.27, U7.P3
SARA_SCL_1.8V1: TP33.P$1, U9.27, U16.P3
SARA_SCL_1.8V2: TP56.P$1, U20.27, U25.P3
SARA_SCL_1.8V3: TP79.P$1, U29.27, U34.P3
SARA_SDA: J14.3, JP8.1, R1.1, U7.P5
SARA_SDA1: J25.3, JP28.1, R50.1, U16.P5
SARA_SDA2: J43.3, JP48.1, R96.1, U25.P5
SARA_SDA3: J61.3, JP68.1, R142.1, U34.P5
SARA_SDA_1.8V: TP9.P$1, U1.26, U7.P4
SARA_SDA_1.8V1: TP32.P$1, U9.26, U16.P4
SARA_SDA_1.8V2: TP55.P$1, U20.26, U25.P4
SARA_SDA_1.8V3: TP78.P$1, U29.26, U34.P4
SARA_TP: R32.1, U1.19
SARA_TP1: R73.1, U9.19
SARA_TP2: R119.1, U20.19
SARA_TP3: R165.1, U29.19
SARA_TXD: IC1.4, R37.1, TP2.P$1
SARA_TXD1: IC4.4, R78.1, TP25.P$1
SARA_TXD2: IC7.4, R124.1, TP48.P$1
SARA_TXD3: IC10.4, R170.1, TP71.P$1
SARA_USB_D+: J18.2, JP4.2, U1.29
SARA_USB_D+1: J33.2, JP24.2, U9.29
SARA_USB_D+2: J51.2, JP44.2, U20.29
SARA_USB_D+3: J69.2, JP64.2, U29.29
SARA_USB_D-: J18.1, JP3.2, U1.28
SARA_USB_D-1: J33.1, JP23.2, U9.28
SARA_USB_D-2: J51.1, JP43.2, U20.28
SARA_USB_D-3: J69.1, JP63.2, U29.28
SARA_VUSB_DET: J18.3, JP5.2, U1.17
SARA_VUSB_DET1: J33.3, JP25.2, U9.17
SARA_VUSB_DET2: J51.3, JP45.2, U20.17
SARA_VUSB_DET3: J69.3, JP65.2, U29.17
SD_!CS!: J11.CS/DAT3, JP10.2, R41.1
SD_!CS!1: J24.CS/DAT3, JP29.2, R87.1
SD_!CS!2: J42.CS/DAT3, JP49.2, R133.1
SD_!CS!3: J60.CS/DAT3, JP69.2, R179.1
SD_PWR: C46.1, J11.VCC, Q6.3, TP23.P$1
SD_PWR1: C27.1, J24.VCC, Q15.3, TP45.P$1
SD_PWR2: C63.1, J42.VCC, Q25.3, TP68.P$1
SD_PWR3: C93.1, J60.VCC, Q35.3, TP91.P$1
SIM_CLK: C8.1, D8.1, J17.C3, U1.38
SIM_CLK1: C41.1, D20.1, J32.C3, U9.38
SIM_CLK2: C76.1, D33.1, J50.C3, U20.38
SIM_CLK3: C106.1, D46.1, J68.C3, U29.38
SIM_IO: C10.2, D8.6, J17.C7, U1.39
SIM_IO1: C42.2, D20.6, J32.C7, U9.39
SIM_IO2: C77.2, D33.6, J50.C7, U20.39
SIM_IO3: C107.2, D46.6, J68.C7, U29.39
SIM_RST: C7.1, D8.4, J17.C2, U1.40
SIM_RST1: C40.1, D20.4, J32.C2, U9.40
SIM_RST2: C75.1, D33.4, J50.C2, U20.40
SIM_RST3: C105.1, D46.4, J68.C2, U29.40
SPI_SCK: IC3.12, J4.57, J5.1, J11.SCLK
SPI_SCK1: IC6.12, J21.1, J24.SCLK, J26.57
SPI_SCK2: IC9.12, J39.1, J42.SCLK, J44.57
SPI_SCK3: IC12.12, J57.1, J60.SCLK, J62.57
SPI_SDI: J4.61, J5.3, J11.DO/DAT0, Q10.3, R22.1
SPI_SDI1: J21.3, J24.DO/DAT0, J26.61, Q11.3, R63.1
SPI_SDI2: J39.3, J42.DO/DAT0, J44.61, Q21.3, R109.1
SPI_SDI3: J57.3, J60.DO/DAT0, J62.61, Q31.3, R155.1
SPI_SDO: IC3.13, J4.59, J5.2, J11.DI/CMD
SPI_SDO1: IC6.13, J21.2, J24.DI/CMD, J26.59
SPI_SDO2: IC9.13, J39.2, J42.DI/CMD, J44.59
SPI_SDO3: IC12.13, J57.2, J60.DI/CMD, J62.59
SWDCK: J2.4, J4.21
SWDCK1: J20.4, J26.21
SWDCK2: J38.4, J44.21
SWDCK3: J56.4, J62.21
SWDIO: J2.2, J4.23
SWDIO1: J20.2, J26.23
SWDIO2: J38.2, J44.23
SWDIO3: J56.2, J62.23
TX1: IC1.13, J4.17, TP6.P$1
TX2: IC4.13, J26.17, TP29.P$1
TX3: IC7.13, J44.17, TP52.P$1
TX4: IC10.13, J62.17, TP75.P$1
USB_D+: J1.A6, J1.B6, J4.3, JP4.1
USB_D+1: J3.A6, J3.B6, J26.3, JP24.1
USB_D+2: J37.A6, J37.B6, J44.3, JP44.1
USB_D+3: J55.A6, J55.B6, J62.3, JP64.1
USB_D-: J1.A7, J1.B7, J4.5, JP3.1
USB_D-1: J3.A7, J3.B7, J26.5, JP23.1
USB_D-2: J37.A7, J37.B7, J44.5, JP43.1
USB_D-3: J55.A7, J55.B7, J62.5, JP63.1
VCCIO: C22.1, C23.1, DSR.3, IC1.1, IC1.7, IC1.16, IC2.2, IC2.7, IC2.16, J6.3, Q5.1, R29.2, R31.1, R42.1, U7.P2
VCCIO1: C58.1, C59.1, DSR1.3, IC4.1, IC4.7, IC4.16, IC5.2, IC5.7, IC5.16, J34.3, Q14.1, R70.2, R72.1, R88.1, U16.P2
VCCIO2: C88.1, C89.1, DSR2.3, IC7.1, IC7.7, IC7.16, IC8.2, IC8.7, IC8.16, J52.3, Q24.1, R116.2, R118.1, R134.1, U25.P2
VCCIO3: C118.1, C119.1, DSR3.3, IC10.1, IC10.7, IC10.16, IC11.2, IC11.7, IC11.16, J70.3, Q34.1, R162.2, R164.1, R180.1, U34.P2
VIN: BYP.2, C1.1, C2.+, C13.1, D5.A, D7.C, F2.2, J4.9, J6.1, R5.2, U2.4, U3.1, U5.8, VIN/3.2, VIN_LED.2
VIN1: BYP1.2, C25.1, C28.1, C29.+, D19.A, D26.C, F1.2, J26.9, J34.1, R54.2, U6.8, U12.4, U15.1, VIN/1.2, VIN_LED1.2
VIN2: BYP2.2, C61.1, C64.1, C65.+, D32.A, D39.C, F3.2, J44.9, J52.1, R100.2, U19.8, U23.4, U24.1, VIN/2.2, VIN_LED2.2
VIN3: BYP3.2, C91.1, C94.1, C95.+, D45.A, D52.C, F4.2, J62.9, J70.1, R146.2, U28.8, U32.4, U33.1, VIN/4.2, VIN_LED3.2
VIN/1: J26.49, R52.2, R53.1
VIN/2: J44.49, R98.2, R99.1
VIN/3: J4.49, R9.2, R10.1
VIN/4: J62.49, R144.2, R145.1
VREG_3.3V: C3.1, C4.1, C5.1, MEAS.1, MEAS.3, U5.1
VREG_3.3V1: C30.1, C32.1, C33.1, MEAS1.1, MEAS1.3, U6.1
VREG_3.3V2: C66.1, C67.1, C68.1, MEAS2.1, MEAS2.3, U19.1
VREG_3.3V3: C96.1, C97.1, C98.1, MEAS3.1, MEAS3.3, U28.1
VSIM: C11.2, C12.2, D8.3, J17.C1, U1.41
VSIM1: C43.2, C44.2, D20.3, J32.C1, U9.41
VSIM2: C78.2, C79.2, D33.3, J50.C1, U20.41
VSIM3: C108.2, C109.2, D46.3, J68.C1, U29.41
V_BATT: C6.1, D7.A, J15.2, J16.1, U2.3, U4.2, U4.3
V_BATT1: C39.1, D26.A, J30.2, J31.1, U12.3, U18.2, U18.3
V_BATT2: C74.1, D39.A, J48.2, J49.1, U23.3, U27.2, U27.3
V_BATT3: C104.1, D52.A, J66.2, J67.1, U32.3, U36.2, U36.3
V_USB: BYP.1, F2.1, J1.VBUS1, J1.VBUS2, JP5.1
V_USB1: BYP1.1, F1.1, J3.VBUS1, J3.VBUS2, JP25.1
V_USB2: BYP2.1, F3.1, J37.VBUS1, J37.VBUS2, JP45.1
V_USB3: BYP3.1, F4.1, J55.VBUS1, J55.VBUS2, JP65.1

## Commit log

2020-09-14 Almost ready for airwire review
2020-09-15 Ready for airwire review
2020-09-18 Updates to support the ESP32 PB
2020-09-21 Work in progress - 14 airwires left!
2020-09-23 Ready for review
2020-09-24 Replaced the Level Shifters
2020-09-25 Rerun panelizer to get correct panel size.
2020-09-29 Added details for the 27pF and 33pF caps.
2020-10-12 Added the missing PROD_IDs
2020-10-13 Updated to use the revised SMD SMA connector footprint
    The footprint for the SMA now includes the toolpath for a 1mm end-mill
2020-10-30 Adding LICENSE.md
2020-10-30 First draft of Example1
2020-10-30 Adding some pin magic to let this run on all the PBs.
2020-11-02 Adding a draft of Example2 - a basic IMU test
2020-11-03 Updating Example2_IMU. Corrected SARA_PWR polarity.
2020-11-03 Added Example3 microSD
2020-11-03 Adding Example4 MAX17048
2020-11-03 Added Example5 Qwiic (Power Switch)
2020-11-03 Added Example6 IO Pins
2020-11-03 Adding Example7 GNSS Antenna Power
2020-11-03 Added Example8 External SPI (Micro OLED)
2020-11-03 Adding Example9 VIN
2020-11-04 Added Example10 IMU Wake_On-Motion
2020-11-05 Adding Example11 GNSS GPRMC
2020-11-05 Adding Example12 Network Info and Example13 Identification
2020-11-06 Added SIM Status reporting with callback. Swapped examples 12 and 13.
2020-11-06 Adding Example14 Register Operator
2020-11-10 Adding Example15 Receive SMS
2020-11-10 Adding Example16 Send SMS
2020-11-17 Adding the Packet Switched Data examples: Ping and HTTP GET/POST
2020-11-19 Minor tweaks
2020-11-19 Updating the examples
2020-11-19 Updates for V11 of the PCB
2020-11-20 Updating the examples for v11 hardware
2020-11-20 Adding updated and extra documentation
2020-11-23 Adding Example20 - Test UART Pins. Uses custom commands to test the IO pins.
2020-11-23 Adding Example21 - Test I2C Pins
2020-11-23 Adding Example22 - bidirectional test of the SARA EXT_INT pin
2020-11-25 Updating Example11. Calling +UTIME=1,1 automatically starts the GPS.
2020-11-25 Updated files for v11 after production review
2020-11-26 Adding production files for v11
2020-12-03 Create MicroMod_Asset_Tracker.zip
    Zip folder of the schematic/board files to upload to Sparkle
2020-12-05 Adding the PROD_ID for the SARA-R510M8S
2021-02-04 Updating Examples 1-5 after testing on V11 hardware
2021-02-04 Revert "Updating Examples 1-5 after testing on V11 hardware"
    This reverts commit 6160b7a9624f28f4c2bda135ea040022309603c5.
2021-02-05 Updating examples 1-9 after testing on V11 hardware
2021-02-06 Final example updates for V11 hardware
2021-02-25 Update README.md
    Updating README for release.
2021-04-20 Correct product image link
2021-09-16 Update README
    Removing NB/IoT feature as the "00B" versions of the SARA-R5 do not support LTE NB-IoT Radio Access Technology, and the LTE FDD bands: 66, 71, 85.
2021-10-06 Add STM32
2021-10-06 Update examples 2-22
2021-10-28 Change BATTVIN3 to 2 so code reads "A2" (PA_1) correctly
2021-12-28 Corrections for v2 of Apollo3 (Artemis)
2021-12-28 Add examples 23 and 24
2022-01-15 Add examples 25-27:
    25: u-blox AssistNow Online - GET and push AssistNow aiding information to an external u-blox GNSS
    26: u-blox AssistNow Offline - GET and push AssistNow aiding information to an external u-blox GNSS
    27: GNSS NTRIP Caster - open a socket to an NTRIP Caster, receive RTCM data and push it to an external GNSS, receive GPGGA NMEA from the GNSS and push to the Caster, all done with callbacks where pos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
2022-01-17 Avoid compiler warnings
2022-01-17 Switch to setSocketReadCallbackPlus - for binary compatibility
2022-01-17 Update AssetTracker_Example25_AssistNowOnline to use the updated getFileContents
2022-01-17 Update AssetTracker_Example26_AssistNowOffline to use the updated getFileContents
2022-01-17 Improve printing on Artemis
2022-01-17 Store the AssistNow file contents and NTRIP credentials in allocated memory - to help reduce stack problems on Mbed OS (Artemis & nRF52840)
2022-01-18 Add Example 28 - works well with all PBs including Artemis (Mbed OS)
2022-04-07 Add Example29 - TCP Ping Pong
